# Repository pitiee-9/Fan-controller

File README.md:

# Fan Controller PCB (KiCad Project)

## Overview

This project is a simple fan controller designed using KiCad as a beginner in PCB design. The goal of this circuit is to control the speed of a DC fan by adjusting the voltage supplied to it. It also helped me understand how different electronic components are connected and how they work together on a printed circuit board.

## How It Works

The circuit regulates the fan speed by controlling the electrical signal that passes through the main integrated circuit (IC). By adjusting the input (through a control component), the output voltage changes, which directly affects how fast the fan spins. Supporting components like resistors, capacitors, and diodes help stabilize, protect, and shape the signal.

## Components and Their Roles

* **_Integrated Circuit (IC)_**
  This is the brain of the circuit. It controls how the signal flows and determines the fan speed based on the input it receives.

* **_Resistors_**
  These limit and control the flow of current in different parts of the circuit. They ensure components receive safe levels of current and help set operating conditions for the IC.

* **_Capacitors_ (Electrolytic and Ceramic)**
  Capacitors store and release electrical energy. In this circuit, they help smooth voltage fluctuations and reduce noise, making the fan run more steadily.

* **_Diode_**
  The diode protects the circuit by allowing current to flow in only one direction. It helps prevent damage from reverse polarity or voltage spikes.

* **_Transistor_**
  Acts as a switch or amplifier. It helps control the amount of current delivered to the fan, especially when higher power is needed.

* **_LED_ (Light Emitting Diode)**
  This is a simple indicator that shows when the circuit is powered and operating.

* **_Connectors / Pins_**
  These are used to connect the power source and the fan to the PCB.

## PCB Design Learning Points

As a beginner, this project helped me learn:

* How to place components logically on a PCB
* How to route tracks (connections) between components
* The importance of proper spacing and clean layout
* Basic circuit design and how real components interact

## Conclusion

This fan controller is a simple but practical project that demonstrates the basics of electronics and PCB design. It is a great starting point for anyone learning KiCad and wanting to build functional hardware projects.

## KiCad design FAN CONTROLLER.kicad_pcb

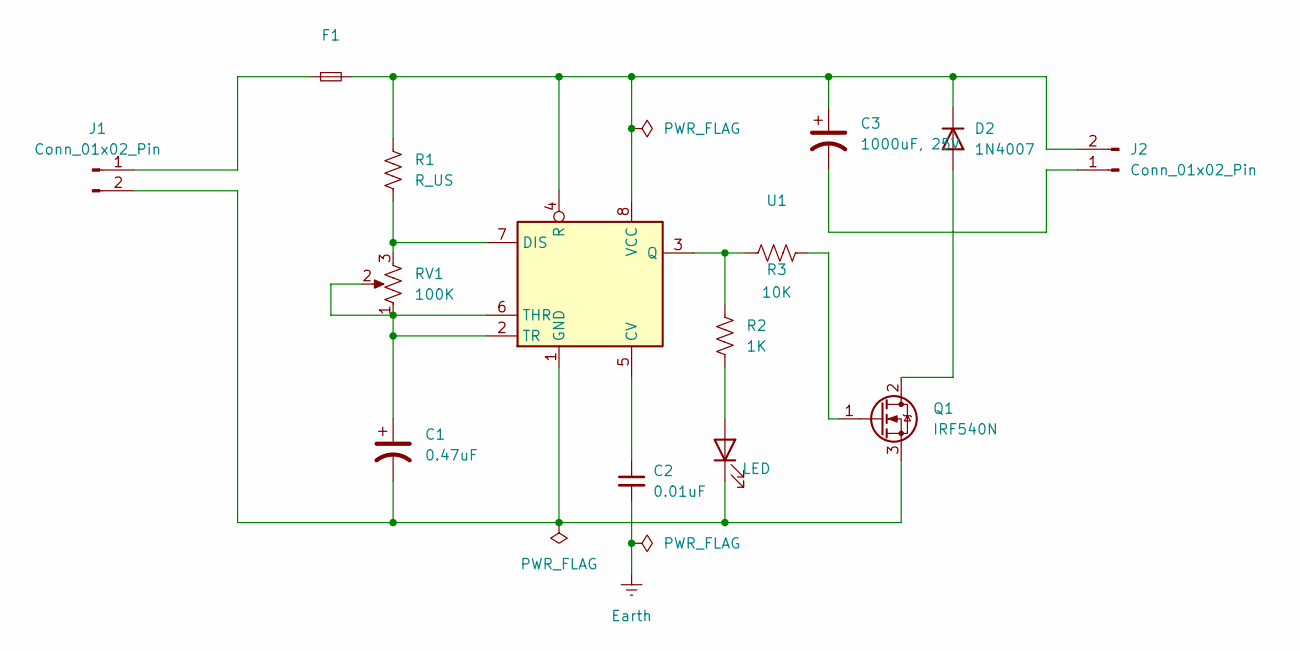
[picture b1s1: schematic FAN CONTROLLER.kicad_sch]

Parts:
C1: 0.47uF; CP_Axial_L10.0mm_D6.0mm_P15.00mm_Horizontal
C2: 0.01uF; CP_Axial_L10.0mm_D6.0mm_P15.00mm_Horizontal
C3: 1000uF, 25V; CP_Radial_D5.0mm_P2.00mm
D1: LED; LED_D3.0mm
D2: 1N4007; D_DO-41_SOD81_P10.16mm_Horizontal
F1: Fuse_Small; Fuse_BelFuse_0ZRE0033FF_L11.4mm_W3.8mm
J1, J2: Conn_01x02_Pin; PinHeader_1x02_P2.54mm_Horizontal
Q1: IRF540N; TO-220-3_Vertical
R1: R_US; R_Axial_DIN0204_L3.6mm_D1.6mm_P7.62mm_Horizontal
R2: 1K; R_Axial_DIN0204_L3.6mm_D1.6mm_P7.62mm_Horizontal
R3: 10K; R_Axial_DIN0204_L3.6mm_D1.6mm_P7.62mm_Horizontal
RV1: 100K; Potentiometer_Vishay_T73XW_Horizontal
U1: NE555D_custom_IC_symbol; SOIC-8_3.9x4.9mm_P1.27mm

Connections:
Earth: C2.2
unnamed: D1.2 (A), R2.2
unnamed: C1.2, D1.1 (K), J1.2, Q1.3 (S), U1.1 (GND)
unnamed: D2.2 (A), Q1.2 (D)
unnamed: C3.1, D2.1 (K), F1.2, J2.2, R1.1, U1.4 (R), U1.8 (VCC)
unnamed: F1.1, J1.1
unnamed: C3.2, J2.1
unnamed: Q1.1 (G), R3.2
unnamed: C2.1, U1.5 (CV)
unnamed: R1.2, RV1.3, U1.7 (DIS)
unnamed: R2.1, R3.1, U1.3 (Q)
unnamed: C1.1, RV1.1, RV1.2, U1.2 (TR), U1.6 (THR)

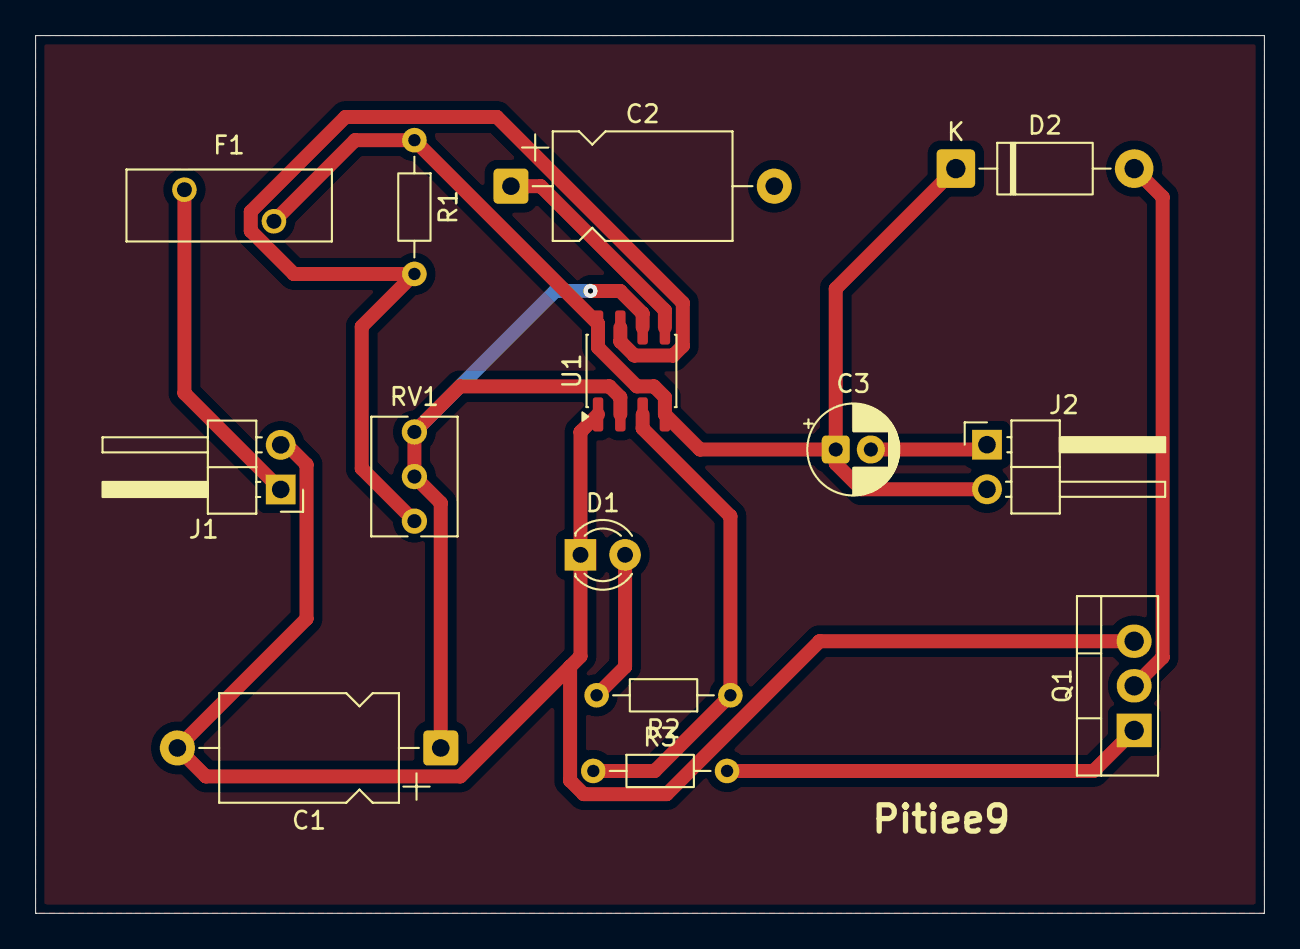
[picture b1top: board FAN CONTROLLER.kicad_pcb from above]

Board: 2 copper layers, 70.0 x 50.0 mm, 14 parts (0 on the bottom side), 11 nets.

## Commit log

2026-03-27 Add README for Fan Controller PCB project
    Added a comprehensive README file for the Fan Controller PCB project, detailing the project overview, functionality, components, learning points, and conclusion.
2026-03-27 Uploaded some files
2026-03-27 Deleted sme unnecessary files
